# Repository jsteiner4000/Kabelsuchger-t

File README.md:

# Kabelsuchgerät (Sender + Handgerät)

Selbstbau-Leitungsortungsgerät für EMA/BMA-Leitungen (J-Y(St)Y, LIYY …):
Ein **Sender** speist ein Suchsignal in eine spannungsfreie Leitung ein, ein
**Handgerät** verfolgt die Leitung von außen, auch durch Wände.

Prinzip (Konzept): Ortung über das **Magnetfeld**. Alle Adern und der Schirm werden gemeinsam gegen Erde
eingespeist, damit kein Rückstrom im selben Kabel das Feld aufhebt. Zwei gekoppelte Töne ermöglichen eine
Stromrichtungsanzeige für volle Trassen. Gebaut wird die **Variante „Einfach“** (ca. 31 € pro Satz): Der Sender
hat zwei Klemmen, ein Display mit Strom in mA und eine Taste. Das Handgerät ist ein Stab mit dem Sensorkopf oben,
einer Ferritspule, zwei Verstärkerstufen und dem eingebauten Wandler des ESP32-S3 mit digitaler
Lock-in-Auswertung.

## Stand

**Phase 3 von 8:** Mini-Test mit den endgültigen Teilen. Julius hat am 13.10.2026 die Variante „Einfach“
freigegeben (E-034 bis E-042), mit Display in beiden Geräten und Aufbau auf Lochraster. Jetzt werden die Teile
für einen Satz bestellt, auf dem Steckbrett getestet und danach auf die Lochrasterplatine übernommen.

## Dokumente

| Datei | Inhalt | Visuell (privat) |
|---|---|---|
| [`docs/lastenheft.md`](docs/lastenheft.md) | Was das Gerät können muss, Abnahmetests mit Zielwerten | <https://claude.ai/artifact/R5hurM3dSdJBk6UaUzjGMM> |
| [`docs/konzept.md`](docs/konzept.md) | Wie es funktioniert: Physik, Einspeisemodi, Signal, Auswertung, Varianten, Reichweiten, Budget | <https://claude.ai/artifact/VZtH7KZhMHQYaksFrRsrAv> |
| [`docs/machbarkeitstest.md`](docs/machbarkeitstest.md) | Mini-Test: Einkaufsliste, Steckbrett-Aufbau, Spule wickeln, Software, Messprogramm M1–M8 | <https://claude.ai/artifact/EqZmsoxrUWFYdXUHB5X285> |
| [`docs/messprotokoll-phase3.md`](docs/messprotokoll-phase3.md) | Messprotokoll zum Ausfüllen | |
| [`docs/variante-einfach.md`](docs/variante-einfach.md) | Variante „Einfach“: was bleibt, was fliegt, Kosten (freigegeben) | |
| [`docs/platine-oder-lochraster.md`](docs/platine-oder-lochraster.md) | KiCad-Entwurf der Platinen, Vergleich mit Lochraster, Empfehlung | <https://claude.ai/artifact/UjBC8Tjy9ur99xCQnq3SMG> |
| [`docs/entscheidungen.md`](docs/entscheidungen.md) | Jede Entscheidung mit Begründung | |
| [`docs/berechnungen/feldmodell.py`](docs/berechnungen/feldmodell.py) | Feld- und Reichweitenrechnung (nur Python-Standardbibliothek) | |
| [`stueckliste.csv`](stueckliste.csv) | Stückliste (ab Phase 4), Trennzeichen `;` | |

## Projektstruktur

```
docs/                          Lastenheft, Konzept, Machbarkeitstest, Entscheidungen, Anleitungen
  berechnungen/                Feldmodell (Python)
hardware/sender/
  testaufbau/                  Schaltplan Sender-Steckbrett (schemdraw-Skript + SVG)
hardware/handgeraet/
  spule/                       Spulenkörper und Wickeldorn (OpenSCAD + STL)
  testaufbau/                  Messkopf (OpenSCAD + STL), Schaltplan Handgerät-Steckbrett
firmware/machbarkeit/
  sender_test/                 Test-Sketch Sender (ESP32-S2 mini, OLED, Strommessung)
  empfaenger_test/             Test-Sketch Handgerät (ESP32-S3, eingebauter Wandler) + lockin.h (Signalverarbeitung)
  test_host/                   Prüfung auf dem PC: Syntaxprüfung + Simulation der ganzen Kette (./build.sh)
firmware/sender/               Endgültige Firmware (Phase 6)
firmware/handgeraet/
hardware/kicad/                KiCad-Entwurf beider Platinen (Schaltplan, Platine, Gerber), Generator-Skript
gehaeuse/                      Gehäuse (Phase 7)
  konzept/                     Ansichtsmodell beider Geräte (OpenSCAD + Bilder)
stueckliste.csv
```

## Phasen

1. Rückfragen und Lastenheft – **erledigt**
2. Konzept – **erledigt**
3. Machbarkeitstest (Mini-Test mit den endgültigen Teilen) – **läuft**
4. Schaltung und Stückliste
5. Lochraster-Aufbauplan (oder Platine nach KiCad-Entwurf, Entscheidung offen)
6. Firmware
7. Gehäuse
8. Inbetriebnahme und Bedienungsanleitung

Nach jeder Phase wird freigegeben, erst dann geht es weiter.

## Sicherheit

Der Sender ist **nur für spannungsfreie Leitungen** gedacht und nicht für Netzspannung ausgelegt.
Beim Steckbrett-Sender bitte Abschnitt 1 von `docs/machbarkeitstest.md` beachten (Masse, Oszilloskop, USB nur bei
ausgeschaltetem Batterieschalter, Pegel MAX nur gegen Erde).

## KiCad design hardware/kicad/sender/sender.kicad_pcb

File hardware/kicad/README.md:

# KiCad-Projekte (Entwurf 1)

Sender und Handgerät der Variante „Einfach“ als KiCad-7-Projekte: Schaltplan, Platine (2 Lagen, nur bedrahtete
Teile), Gerber-Dateien. **Entwurf vor dem Mini-Test – noch nicht bestellen.** Was vorher zu prüfen ist, steht in
[`docs/platine-oder-lochraster.md`](../../docs/platine-oder-lochraster.md).

| Ordner | Inhalt |
|---|---|
| `handgeraet/` | `handgeraet.kicad_pro` (öffnen), Schaltplan, Platine 34 × 70 mm, `handgeraet-gerber.zip`, `handgeraet-schaltplan.pdf`, `handgeraet-drc.txt`, Bilder |
| `sender/` | dasselbe für den Sender, Platine 80 × 60 mm |
| `lib/` | eigene Symbole und Footprints für ESP32-S3 SuperMini und LOLIN S2 mini |
| `netze.py` | Netzliste beider Geräte (gleiche Bauteilnummern wie die Steckbrett-Schaltpläne) |
| `platzierung.py` | Lage der Bauteile |
| `erzeuge.py` | erzeugt alles neu: Schaltplan, Platine, Routing (Freerouting), DRC, Gerber, Bilder |

## Öffnen

KiCad 7 oder neuer installieren und die `.kicad_pro`-Datei öffnen. Die eigene Bibliothek wird über die
Projekt-Bibliothekstabellen automatisch gefunden. KiCad 8/9 fragen beim Öffnen, ob das Format umgestellt werden soll;
das ist in Ordnung.

Der Schaltplan verbindet über Netznamen (keine Linien). Die gut lesbaren Zeichnungen sind die
Steckbrett-Schaltpläne in `hardware/sender/testaufbau/` und `hardware/handgeraet/testaufbau/`.

## Prüfung (DRC)

Beide Platinen: **0 offene Verbindungen, keine Abstands- oder Kurzschlussfehler.** Die übrigen Meldungen in
`*-drc.txt` sind:

- `silk_overlap`, `silk_over_copper`: Beschriftungen überlappen sich oder liegen auf Lötaugen (nur Optik)
- `lib_footprint_issues`: In der Erzeugungsumgebung war keine globale Bibliothekstabelle eingerichtet; auf einem
  normalen KiCad-Rechner entfällt das
- `starved_thermal`: An 1–2 Massepads hat die Wärmefalle nur einen statt zwei Stege; die Verbindung besteht trotzdem

## Bestellen (erst nach dem Mini-Test)

Bei JLCPCB oder einem ähnlichen Anbieter die beiden `*-gerber.zip` hochladen: 2 Lagen, 1,6 mm, HASL (bleifrei
optional), Farbe beliebig, 5 Stück. Ca. 9–12 € für beide inkl. Versand, 1–3 Wochen Lieferzeit.

## Neu erzeugen

Voraussetzungen: KiCad 7 (Python-Modul `pcbnew`, `kicad-cli`), Java 25 und Freerouting 2.4 mit Abhängigkeiten
(Maven: `app.freerouting:freerouting:2.4.1`).

```
export FREEROUTING_CP="/pfad/zu/freerouting/lib/*"
export FREEROUTING_JAVA=/usr/lib/jvm/java-25-openjdk-amd64/bin/java
python3 erzeuge.py                 # beide Geräte
python3 erzeuge.py sender          # nur der Sender
python3 erzeuge.py --kein-routing  # nur Platzierung prüfen
```

Freerouting arbeitet nicht deterministisch; das Skript wiederholt bis zu fünfmal, bis alles verbunden ist. Die
Leiterbahnen sehen deshalb nach jedem Lauf etwas anders aus.

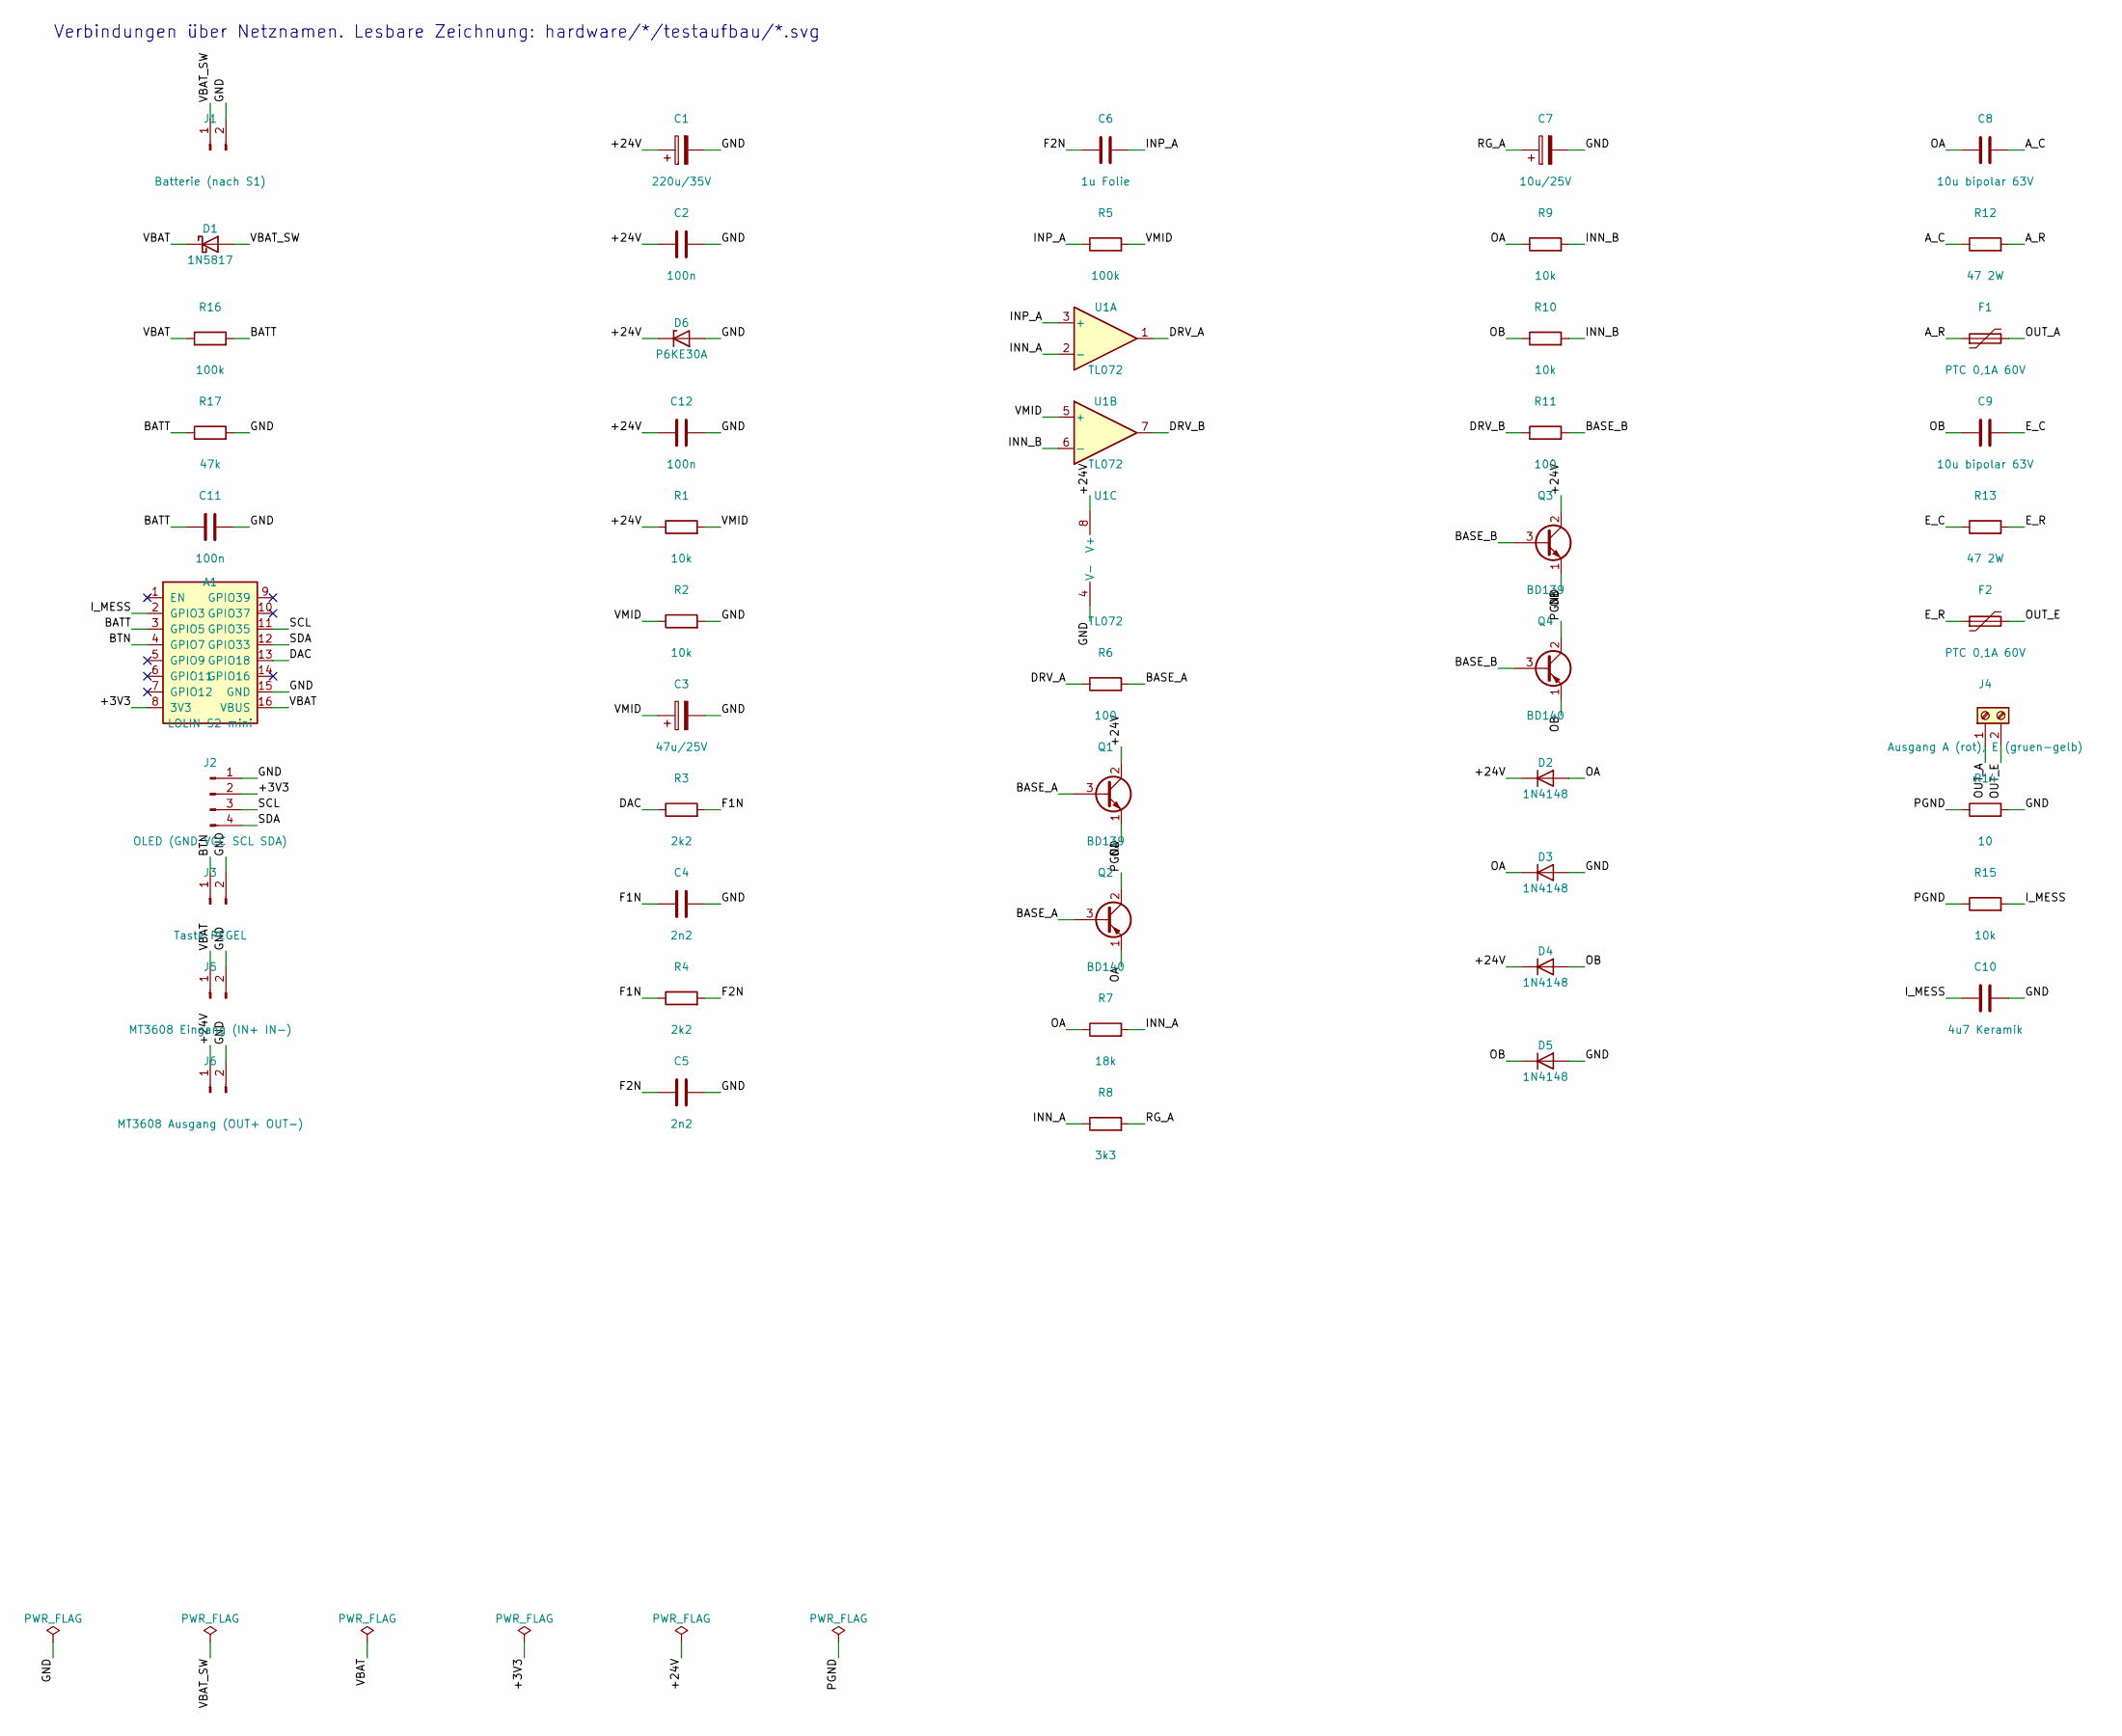
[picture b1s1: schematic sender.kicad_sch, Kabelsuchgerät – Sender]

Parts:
A1: LOLIN S2 mini; LOLIN_S2_mini
C1: 220u/35V; CP_Radial_D8.0mm_P3.50mm
C2, C11, C12: 100n; C_Disc_D3.0mm_W2.0mm_P2.50mm
C3: 47u/25V; CP_Radial_D6.3mm_P2.50mm
C4, C5: 2n2; C_Disc_D3.0mm_W2.0mm_P2.50mm
C6: 1u Folie; C_Rect_L7.2mm_W5.5mm_P5.00mm_FKS2_FKP2_MKS2_MKP2
C7: 10u/25V; CP_Radial_D5.0mm_P2.00mm
C8, C9: 10u bipolar 63V; C_Radial_D8.0mm_H11.5mm_P3.50mm
C10: 4u7 Keramik; C_Disc_D5.0mm_W2.5mm_P5.00mm
D1: 1N5817; D_DO-41_SOD81_P5.08mm_Vertical_KathodeUp
D2, D3, D4, D5: 1N4148; D_DO-35_SOD27_P2.54mm_Vertical_KathodeUp
D6: P6KE30A; D_DO-15_P5.08mm_Vertical_KathodeUp
F1, F2: PTC 0,1A 60V; C_Disc_D7.5mm_W5.0mm_P5.00mm
J1: Batterie (nach S1); PinHeader_1x02_P2.54mm_Vertical
J2: OLED (GND VCC SCL SDA); PinHeader_1x04_P2.54mm_Vertical
J3: Taste PEGEL; PinHeader_1x02_P2.54mm_Vertical
J4: Ausgang A (rot), E (gruen-gelb); TerminalBlock_Phoenix_MKDS-1,5-2-5.08_1x02_P5.08mm_Horizont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
J5: MT3608 Eingang (IN+ IN-); PinHeader_1x02_P2.54mm_Vertical
J6: MT3608 Ausgang (OUT+ OUT-); PinHeader_1x02_P2.54mm_Vertical
Q1, Q3: BD139; TO-126-3_Vertical
Q2, Q4: BD140; TO-126-3_Vertical
R1, R2, R9, R10, R15: 10k; R_Axial_DIN0207_L6.3mm_D2.5mm_P2.54mm_Vertical
R3, R4: 2k2; R_Axial_DIN0207_L6.3mm_D2.5mm_P2.54mm_Vertical
R5, R16: 100k; R_Axial_DIN0207_L6.3mm_D2.5mm_P2.54mm_Vertical
R6, R11: 100; R_Axial_DIN0207_L6.3mm_D2.5mm_P2.54mm_Vertical
R7: 18k; R_Axial_DIN0207_L6.3mm_D2.5mm_P2.54mm_Vertical
R8: 3k3; R_Axial_DIN0207_L6.3mm_D2.5mm_P2.54mm_Vertical
R12, R13: 47 2W; R_Axial_DIN0617_L17.0mm_D6.0mm_P5.08mm_Vertical
R14: 10; R_Axial_DIN0207_L6.3mm_D2.5mm_P2.54mm_Vertical
R17: 47k; R_Axial_DIN0207_L6.3mm_D2.5mm_P2.54mm_Vertical
U1: TL072; DIP-8_W7.62mm

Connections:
+3V3: A1.8 (3V3), J2.2
+24V: C1.1, C2.1, C12.1, D2.1 (K), D4.1 (K), D6.1 (K), J6.1, Q1.2 (C), Q3.2 (C), R1.1, U1.8 (V+)
A_C: C8.2, R12.1
A_R: F1.1, R12.2
BASE_A: Q1.3 (B), Q2.3 (B), R6.2
BASE_B: Q3.3 (B), Q4.3 (B), R11.2
BATT: A1.3 (GPIO5), C11.1, R16.2, R17.1
BTN: A1.4 (GPIO7), J3.1
DAC: A1.13 (GPIO18), R3.1
DRV_A: R6.1, U1.1
DRV_B: R11.1, U1.7
E_C: C9.2, R13.1
E_R: F2.1, R13.2
F1N: C4.1, R3.2, R4.1
F2N: C5.1, C6.1, R4.2
GND: A1.15 (GND), C1.2, C2.2, C3.2, C4.2, C5.2, C7.2, C10.2, C11.2, C12.2, D3.2 (A), D5.2 (A), D6.2 (A), J1.2, J2.1, J3.2, J5.2, J6.2, R2.2, R14.2, R17.2, U1.4 (V-)
INN_A: R7.2, R8.1, U1.2 (-)
INN_B: R9.2, R10.2, U1.6 (-)
INP_A: C6.2, R5.1, U1.3 (+)
I_MESS: A1.2 (GPIO3), C10.1, R15.2
OA: C8.1, D2.2 (A), D3.1 (K), Q1.1 (E), Q2.1 (E), R7.1, R9.1
OB: C9.1, D4.2 (A), D5.1 (K), Q3.1 (E), Q4.1 (E), R10.1
OUT_A: F1.2, J4.1
OUT_E: F2.2, J4.2
PGND: Q2.2 (C), Q4.2 (C), R14.1, R15.1
RG_A: C7.1, R8.2
SCL: A1.11 (GPIO35), J2.3
SDA: A1.12 (GPIO33), J2.4
VBAT: A1.16 (VBUS), D1.1 (K), J5.1, R16.1
VBAT_SW: D1.2 (A), J1.1
VMID: C3.1, R1.2, R2.1, R5.2, U1.5 (+)

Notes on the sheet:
Verbindungen über Netznamen. Lesbare Zeichnung: hardware/*/testaufbau/*.svg

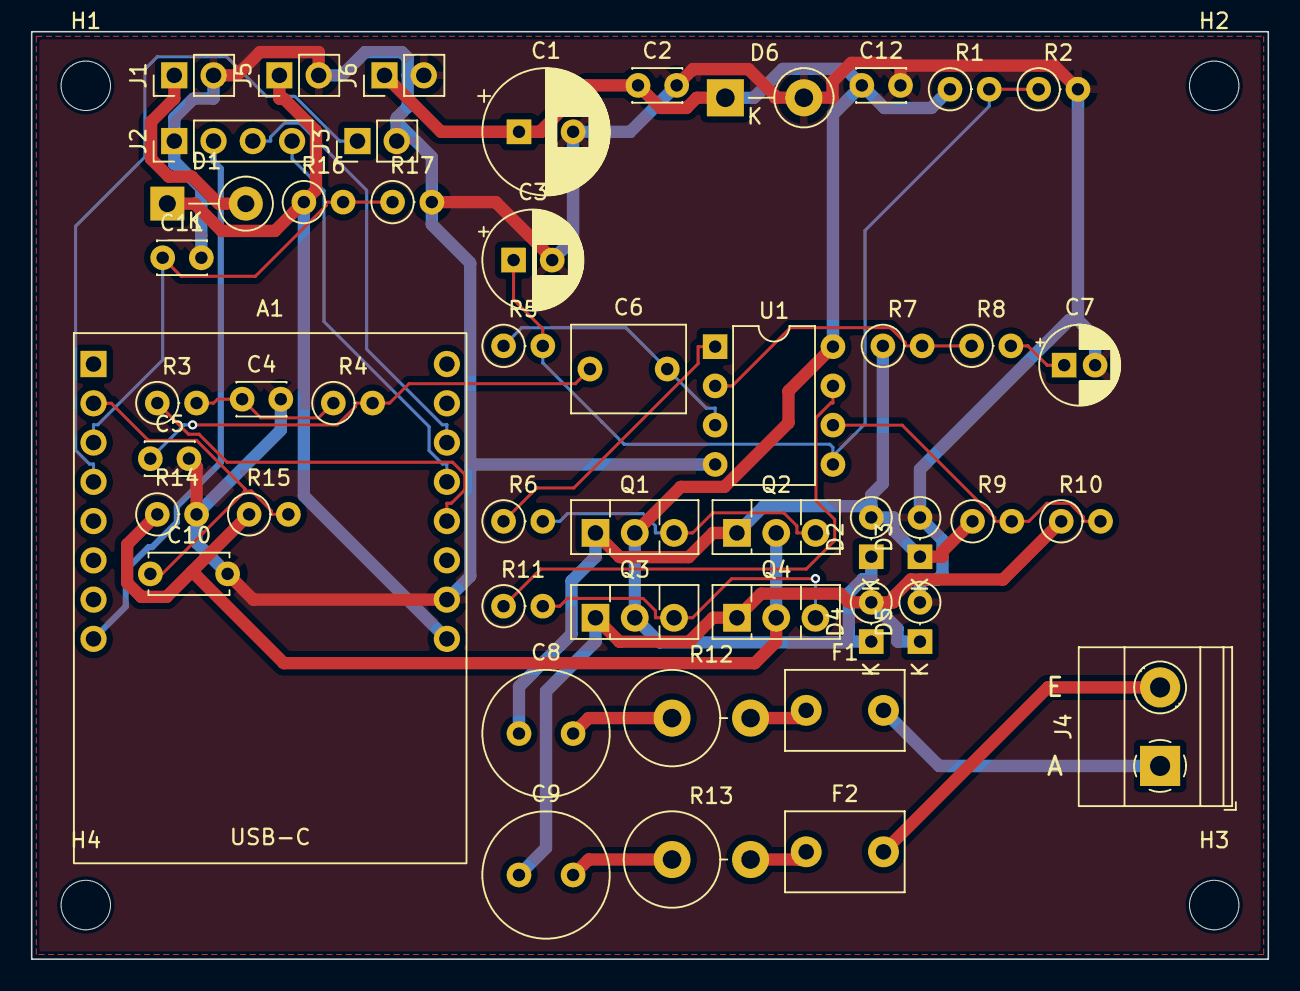
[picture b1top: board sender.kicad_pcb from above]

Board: 2 copper layers, 80.0 x 60.0 mm, 53 parts (0 on the bottom side), 31 nets.

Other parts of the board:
H1, H2, H3, H4: M3; MountingHole_3.2mm_M3

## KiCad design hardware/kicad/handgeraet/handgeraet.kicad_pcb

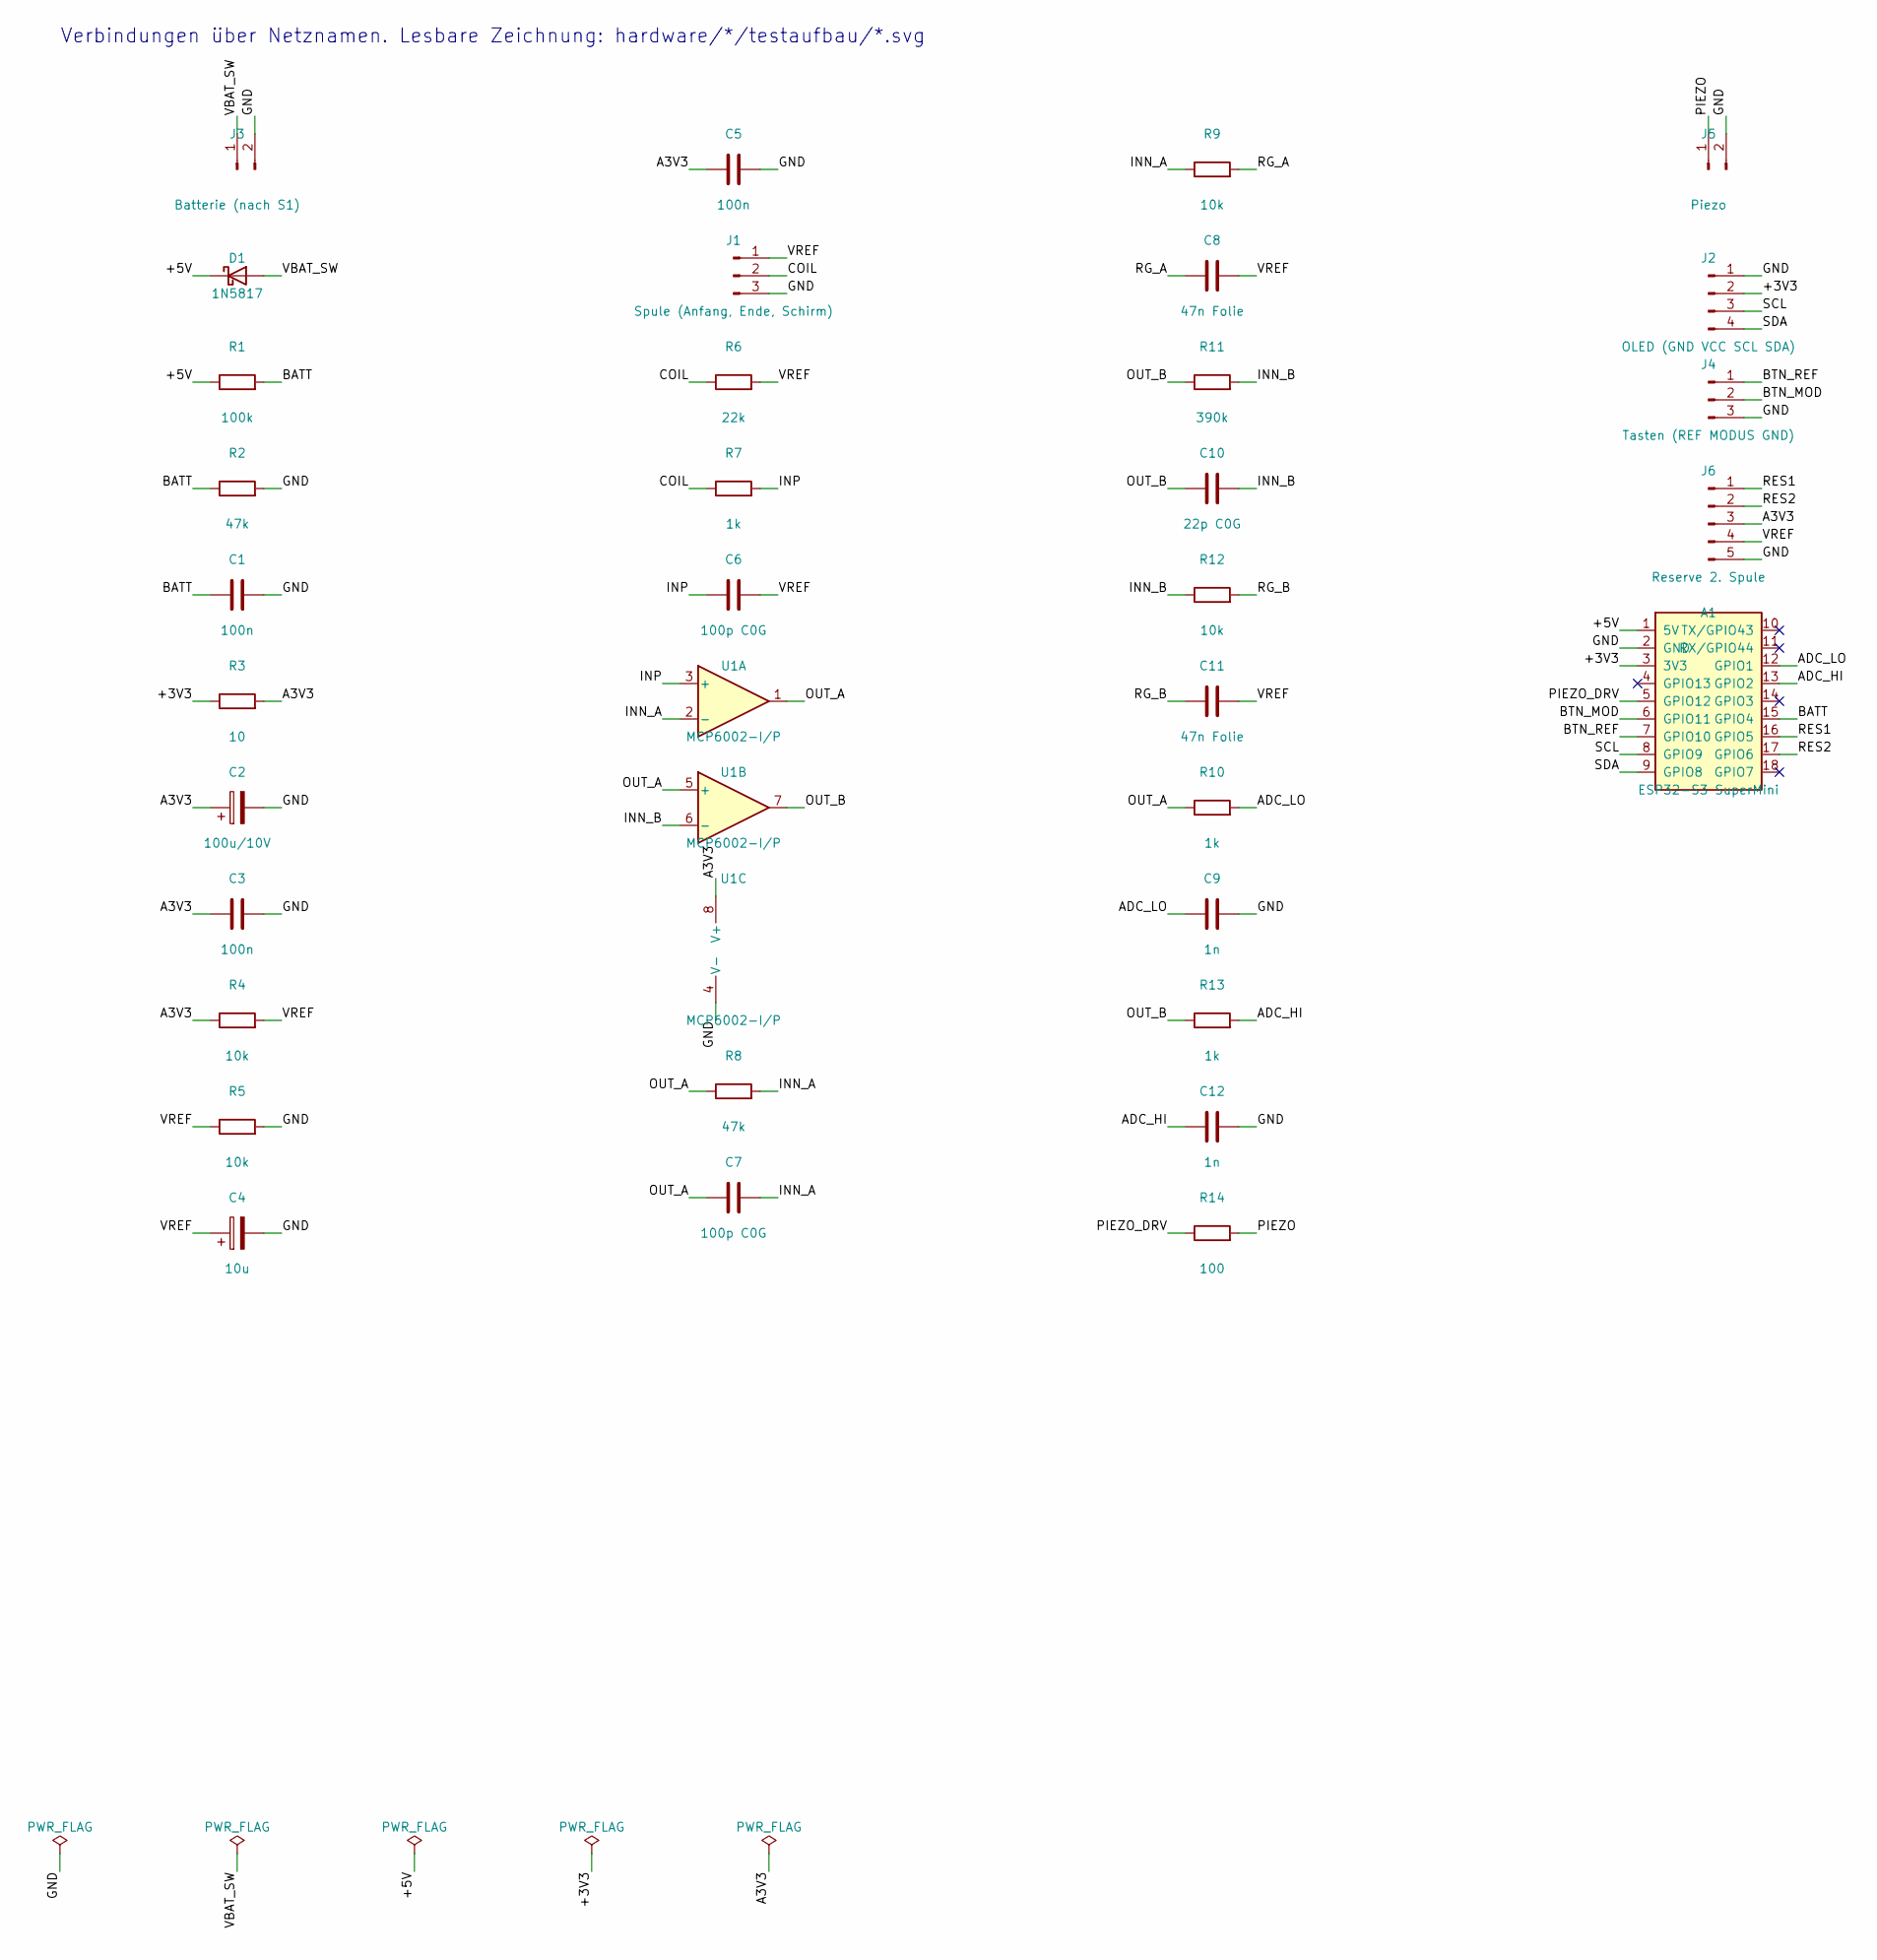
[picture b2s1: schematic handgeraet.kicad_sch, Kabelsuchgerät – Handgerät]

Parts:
A1: ESP32-S3 SuperMini; ESP32-S3_SuperMini
C1, C3, C5: 100n; C_Disc_D3.0mm_W2.0mm_P2.50mm
C2: 100u/10V; CP_Radial_D5.0mm_P2.00mm
C4: 10u; CP_Radial_D5.0mm_P2.00mm
C6, C7: 100p C0G; C_Disc_D3.0mm_W2.0mm_P2.50mm
C8, C11: 47n Folie; C_Rect_L7.2mm_W2.5mm_P5.00mm_FKS2_FKP2_MKS2_MKP2
C9, C12: 1n; C_Disc_D3.0mm_W2.0mm_P2.50mm
C10: 22p C0G; C_Disc_D3.0mm_W2.0mm_P2.50mm
D1: 1N5817; D_DO-41_SOD81_P5.08mm_Vertical_KathodeUp
J1: Spule (Anfang, Ende, Schirm); PinHeader_1x03_P2.54mm_Vertical
J2: OLED (GND VCC SCL SDA); PinHeader_1x04_P2.54mm_Vertical
J3: Batterie (nach S1); PinHeader_1x02_P2.54mm_Vertical
J4: Tasten (REF MODUS GND); PinHeader_1x03_P2.54mm_Vertical
J5: Piezo; PinHeader_1x02_P2.54mm_Vertical
J6: Reserve 2. Spule; PinHeader_1x05_P2.54mm_Vertical
R1: 100k; R_Axial_DIN0207_L6.3mm_D2.5mm_P2.54mm_Vertical
R2, R8: 47k; R_Axial_DIN0207_L6.3mm_D2.5mm_P2.54mm_Vertical
R3: 10; R_Axial_DIN0207_L6.3mm_D2.5mm_P2.54mm_Vertical
R4, R5, R9, R12: 10k; R_Axial_DIN0207_L6.3mm_D2.5mm_P2.54mm_Vertical
R6: 22k; R_Axial_DIN0207_L6.3mm_D2.5mm_P2.54mm_Vertical
R7, R10, R13: 1k; R_Axial_DIN0207_L6.3mm_D2.5mm_P2.54mm_Vertical
R11: 390k; R_Axial_DIN0207_L6.3mm_D2.5mm_P2.54mm_Vertical
R14: 100; R_Axial_DIN0207_L6.3mm_D2.5mm_P2.54mm_Vertical
U1: MCP6002-I/P; DIP-8_W7.62mm

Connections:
+3V3: A1.3 (3V3), J2.2, R3.1
+5V: A1.1 (5V), D1.1 (K), R1.1
A3V3: C2.1, C3.1, C5.1, J6.3, R3.2, R4.1, U1.8 (V+)
ADC_HI: A1.13 (GPIO2), C12.1, R13.2
ADC_LO: A1.12 (GPIO1), C9.1, R10.2
BATT: A1.15 (GPIO4), C1.1, R1.2, R2.1
BTN_MOD: A1.6 (GPIO11), J4.2
BTN_REF: A1.7 (GPIO10), J4.1
COIL: J1.2, R6.1, R7.1
GND: A1.2 (GND), C1.2, C2.2, C3.2, C4.2, C5.2, C9.2, C12.2, J1.3, J2.1, J3.2, J4.3, J5.2, J6.5, R2.2, R5.2, U1.4 (V-)
INN_A: C7.2, R8.2, R9.1, U1.2 (-)
INN_B: C10.2, R11.2, R12.1, U1.6 (-)
INP: C6.1, R7.2, U1.3 (+)
OUT_A: C7.1, R8.1, R10.1, U1.1, U1.5 (+)
OUT_B: C10.1, R11.1, R13.1, U1.7
PIEZO: J5.1, R14.2
PIEZO_DRV: A1.5 (GPIO12), R14.1
RES1: A1.16 (GPIO5), J6.1
RES2: A1.17 (GPIO6), J6.2
RG_A: C8.1, R9.2
RG_B: C11.1, R12.2
SCL: A1.8 (GPIO9), J2.3
SDA: A1.9 (GPIO8), J2.4
VBAT_SW: D1.2 (A), J3.1
VREF: C4.1, C6.2, C8.2, C11.2, J1.1, J6.4, R4.2, R5.1, R6.2

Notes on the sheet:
Verbindungen über Netznamen. Lesbare Zeichnung: hardware/*/testaufbau/*.svg

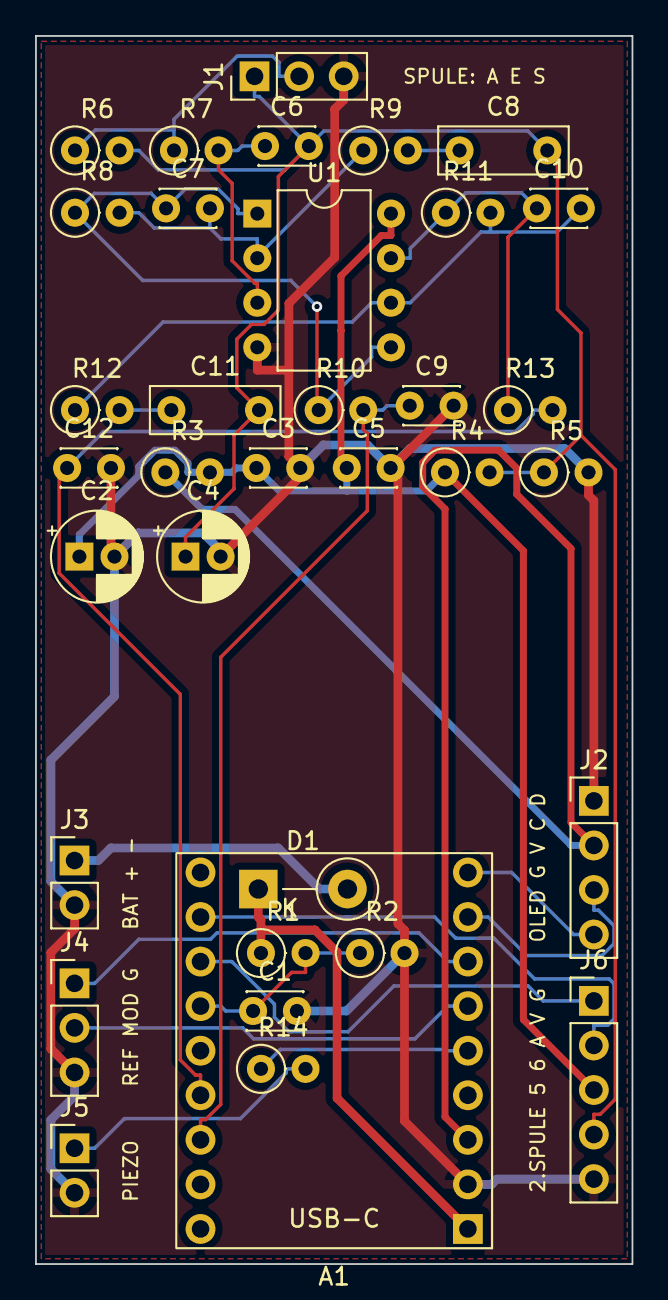
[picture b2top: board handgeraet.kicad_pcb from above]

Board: 2 copper layers, 34.0 x 70.0 mm, 35 parts (0 on the bottom side), 25 nets.

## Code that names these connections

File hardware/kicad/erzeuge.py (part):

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MODULE = {
    # Name: (Pins links [(Nr, Name)], Pins rechts, Footprint-Beschreibung)
    'ESP32-S3_SuperMini': (
        [('1', '5V'), ('2', 'GND'), ('3', '3V3'), ('4', 'GPIO13'), ('5', 'GPIO12'), ('6', 'GPIO11'),
         ('7', 'GPIO10'), ('8', 'GPIO9'), ('9', 'GPIO8')],
        [('10', 'TX/GPIO43'), ('11', 'RX/GPIO44'), ('12', 'GPIO1'), ('13', 'GPIO2'), ('14', 'GPIO3'),
         ('15', 'GPIO4'), ('16', 'GPIO5'), ('17', 'GPIO6'), ('18', 'GPIO7')],
        'ESP32-S3 SuperMini, 2 x 9 Pins, Reihenabstand 15,24 mm, USB-C am Pin-1-Ende. '
        'BELEGUNG UND REIHENABSTAND VOR DER BESTELLUNG AM GELIEFERTEN MODUL PRUEFEN.'),
    'LOLIN_S2_mini': (
        [('1', 'EN'), ('2', 'GPIO3'), ('3', 'GPIO5'), ('4', 'GPIO7'), ('5', 'GPIO9'), ('6', 'GPIO11'),
         ('7', 'GPIO12'), ('8', '3V3')],
        [('9', 'GPIO39'), ('10', 'GPIO37'), ('11', 'GPIO35'), ('12', 'GPIO33'), ('13', 'GPIO18'),
         ('14', 'GPIO16'), ('15', 'GND'), ('16', 'VBUS')],
        'LOLIN S2 mini, nur die beiden aeusseren Reihen (D1-mini-kompatibel, 22,86 mm), USB-C unten. '
        'BELEGUNG VOR DER BESTELLUNG AM GELIEFERTEN MODUL PRUEFEN.'),
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
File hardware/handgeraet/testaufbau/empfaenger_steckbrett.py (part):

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    d += elm.Line().right(1.4).at(o2)

    # Ausgänge zu den Wandlereingängen, je mit RC gegen GND (Ladungsreserve für den Wandler)
    for (o, r, c, txt) in ((o1, 'R10\n1 kΩ', 'C9\n1 nF', 'NIEDRIG (GPIO1)'), (o2, 'R13\n1 kΩ', 'C12\n1 nF', 'HOCH (GPIO2)')):
        tp = (o[0] + 1.4, o[1])
        d += elm.Dot().at(tp)
        d += elm.Line().up(3.0).at(tp)
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        elm.IcPin(name='3V3', side='left', pos=0.62, anchorname='v33'),
        elm.IcPin(name='GND', side='left', pos=0.38, anchorname='gnd'),
        elm.IcPin(name='USB-C', side='left', pos=0.12, anchorname='usb'),
        elm.IcPin(name='GPIO1', side='right', pos=0.93, anchorname='g1'),
        elm.IcPin(name='GPIO2', side='right', pos=0.81, anchorname='g2'),
        elm.IcPin(name='GPIO4', side='right', pos=0.69, anchorname='g4'),
        elm.IcPin(name='GPIO8', side='right', pos=0.55, anchorname='g8'),
        elm.IcPin(name='GPIO9', side='right', pos=0.43, anchorname='g9'),
        elm.IcPin(name='GPIO10', side='right', pos=0.29, anchorname='g10'),
        elm.IcPin(name='GPIO11', side='right', pos=0.17, anchorname='g11'),
        elm.IcPin(name='GPIO12', side='right', pos=0.05, anchorname='g12')],
        size=(4.6, 10.0), label='ESP32-S3\nSuperMini').right().at((0.5, ys)))
    net(d, s3.v5, '5V', direction='left', length=0.8)
    net(d, s3.v33, '3V3', direction='left', length=0.8)
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    net(d, s3.g1, 'NIEDRIG', direction='right', length=1.0)
    net(d, s3.g2, 'HOCH', direction='right', length=1.0)
    net(d, s3.g4, 'BATT', direction='right', length=1.0)
    d += elm.Label().at((s3.g4[0] + 0.3, s3.g4[1] - 0.55)).label('GPIO5/6: Reserve 2. Spule', loc='right', fontsize=8)

    # OLED
    xo = s3.g8[0] + 4.2
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        d += elm.Line().right().to((xr, pin[1]))
        d += elm.Dot()
    d += elm.Resistor().right().at(s3.g12).label('R14 100 Ω', loc='top', fontsize=9)
    d += elm.Crystal().right().to((xr, s3.g12[1])).label('BZ1 Piezo', loc='bottom', fontsize=9)
    d += elm.Line().up().at((xr, s3.g12[1])).to((xr, s3.g10[1]))
    gnd(d, (xr, s3.g12[1]), length=0.5)

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    d += elm.Resistor().right().at((xa3, ya3)).label('R3 10 Ω', loc='top')
    d += elm.Dot()
    a3 = d.here
    d += elm.Label().at((a3[0], a3[1] + 0.35)).label('A3V3', loc='top', fontsize=10)
    d += elm.Capacitor(polar=True).down().at(a3).label('C2\n100 µF', loc='bottom')
    d += elm.Ground()
    d += elm.Line().right(1.6).at(a3)
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        'U1 = MCP6002 (DIP-8). Spule über geschirmtes Kabel (Schirm nur hier an GND). Ruhepegel an Pin 1 und 7: 1,65 V.',
        loc='right', fontsize=10)
    d += elm.Label().at((-2.0, ys - 7.8)).label(
        'Messpunkte: TPE1 = VREF · TPE2 = U1 Pin 1 (NIEDRIG) · TPE3 = U1 Pin 7 (HOCH) · TPE4 = BATT.  '
        'USB nur bei S1 = AUS anstecken.',
        loc='right', fontsize=10)
print('geschrieben:', OUT)
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
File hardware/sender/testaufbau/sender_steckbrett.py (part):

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                            elm.IcPin(name='3V3', side='left', pos=0.66, anchorname='v33'),
                            elm.IcPin(name='GND', side='left', pos=0.44, anchorname='gnd'),
                            elm.IcPin(name='USB-C', side='left', pos=0.18, anchorname='usb'),
                            elm.IcPin(name='GPIO33', side='right', pos=0.92, anchorname='g33'),
                            elm.IcPin(name='GPIO35', side='right', pos=0.79, anchorname='g35'),
                            elm.IcPin(name='GPIO7', side='right', pos=0.56, anchorname='g7'),
                            elm.IcPin(name='GPIO5', side='right', pos=0.37, anchorname='g5'),
                            elm.IcPin(name='GPIO3', side='right', pos=0.24, anchorname='g3'),
                            elm.IcPin(name='GPIO18', side='right', pos=0.08, anchorname='dac')],
                      size=(4.4, 7.0), label='ESP32-S2\nmini').anchor('vbus').at((vbat[0] + 5.0, vbat[1])))
    d += elm.Line().at(vbat).to(s2.vbus)
    d += elm.Line().left(0.6).at(s2.gnd)
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    # ================= Hochsetzsteller und 24-V-Schiene (oben Mitte)
    xm = 21.5
    ym = 14.0
    mt = d.add(elm.Ic(pins=[elm.IcPin(side='left', anchorname='inp'),
                            elm.IcPin(side='right', anchorname='outp'),
                            elm.IcPin(side='bot', anchorname='gnd')],
                      size=(3.0, 1.5), label='MT3608\n→ 24,0 V').anchor('inp').at((xm, ym)))
    d += elm.Ground().at(mt.gnd)
    net(d, mt.inp, 'VBAT', direction='left', length=1.0)
    y24 = mt.outp[1]
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    d += elm.Capacitor(polar=True).down().label('C3\n47 µF', loc='bottom')
    d += elm.Ground()
    d += elm.Line().left().at(vm).to((xb - 0.8, vm[1]))
    d += elm.Label().label('VMID = 12 V', loc='left')

    # ================= Tiefpass, Kanal A (Zeile y = 6)
    y = 6.0
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    d += elm.Dot()
    ina = d.here
    d += elm.Resistor().up().at(ina).label('R5\n100 kΩ', loc='bottom')
    d += elm.Vdd().up().label('VMID')
    d += elm.Line().right().at(ina).to((ina[0] + 1.0, ina[1]))
    ua = d.add(elm.Opamp(leads=True).right().flip().anchor('in2').label('U1A', loc='center', ofst=(-0.4, 0), fontsize=9))
    pin_no(d, ua.in2, '3', dx=0.2)
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    pin_no(d, ub.in2, '5', dx=-0.2, dy=-0.55)
    pin_no(d, ub.out, '7', dx=0.2)
    d += elm.Line().right().at(ub.in2).to((n6[0] + 0.3, ub.in2[1]))
    d += elm.Vdd().right().label('VMID', loc='right')
    d += elm.Resistor().left().at(ub.out).label('R11\n100 Ω')
    d += elm.Dot()
    b2 = d.here
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    # ================= Strommessung (unten links)
    xs = -6.0
    ysm = yr10 - 1.0
    d += elm.Label().at((xs, ysm)).label('PGND', loc='left', fontsize=10)
    d += elm.Dot().at((xs, ysm))
    d += elm.Resistor().down().at((xs, ysm)).label('R14\n10 Ω', loc='bottom')
    d += elm.Ground()
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        'MT3608 vor dem Aufbau auf 24,0 V einstellen.',
        loc='right', fontsize=10)
    d += elm.Label().at((-8.0, ysm - 7.8)).label(
        'Messpunkte: TP1 = GPIO18, TP2 = nach R4, TP3 = OA, TP4 = OB, TP5 = PGND (Strom: Mittelwert = Spannung ÷ 10 Ω).  '
        'USB nur bei S1 = AUS anstecken.',
        loc='right', fontsize=10)
print('geschrieben:', OUT)
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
